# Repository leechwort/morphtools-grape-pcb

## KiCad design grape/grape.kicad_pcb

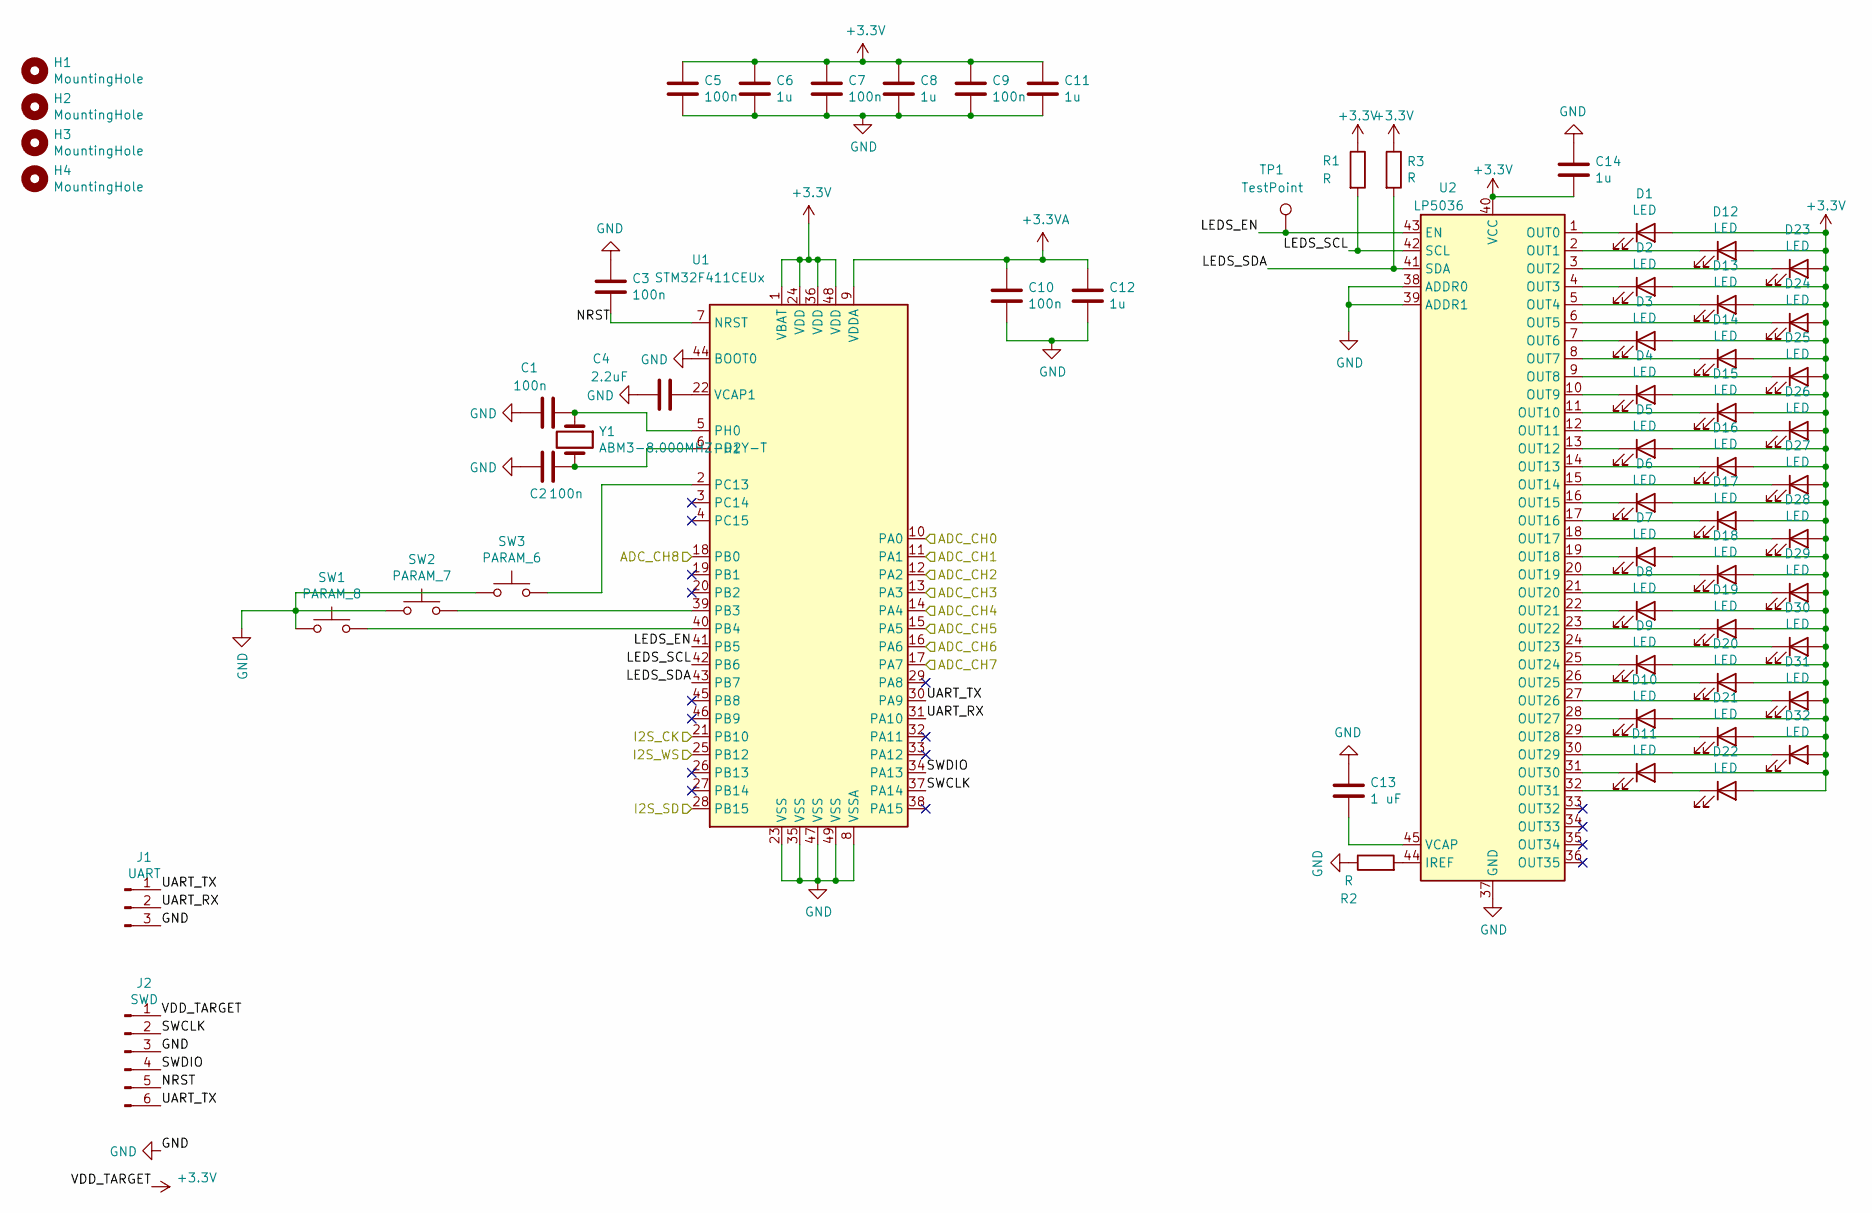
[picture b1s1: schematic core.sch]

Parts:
C1, C2, C3, C5, C7, C9, C10: 100n; C_0805_2012Metric_Pad1.18x1.45mm_HandSolder
C4: 2.2uF; C_0805_2012Metric_Pad1.18x1.45mm_HandSolder
C6, C8, C11, C12, C14: 1u; C_0805_2012Metric_Pad1.18x1.45mm_HandSolder
C13: 1 uF; C_0805_2012Metric_Pad1.18x1.45mm_HandSolder
D1, D2, D3, D4, D5, D6, D7, D8, D9, D10, D11, D12, D13, D14, D15, D16, D17, D18, D19, D20, D21, D22, D23, D24, D25, D26, D27, D28, D29, D30, D31, D32: LED; LED_D3.0mm
H1, H2, H3, H4: MountingHole; MountingHole_3.2mm_M3_Pad_Via
J1: UART; Molex_PicoBlade_53047-0310_1x03_P1.25mm_Vertical
J2: SWD; Molex_PicoBlade_53047-0610_1x06_P1.25mm_Vertical
R1, R2, R3: R; R_0805_2012Metric_Pad1.20x1.40mm_HandSolder
SW1: PARAM_8; SW_SPST_TL3305A
SW2: PARAM_7; SW_SPST_TL3305A
SW3: PARAM_6; SW_SPST_TL3305A
TP1: TestPoint; TestPoint_Pad_D1.5mm
U1: STM32F411CEUx; QFN-48-1EP_7x7mm_P0.5mm_EP5.6x5.6mm
U2: LP5036; VQFN-46-1EP_5x6mm_P0.4mm_EP2.8x3.8mm
Y1: ABM3-8.000MHZ-D2Y-T; Crystal_SMD_5032-2Pin_5.0x3.2mm_HandSoldering

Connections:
+3.3VA: C10.1, C12.1, U1.9 (VDDA); also elsewhere on the board
+3V3: C5.1, C6.1, C7.1, C8.1, C9.1, C11.1, C14.2, D1.2 (A), D2.2 (A), D3.2 (A), D4.2 (A), D5.2 (A), D6.2 (A), D7.2 (A), D8.2 (A), D9.2 (A), D10.2 (A), D11.2 (A), D12.2 (A), D13.2 (A), D14.2 (A), D15.2 (A), D16.2 (A), D17.2 (A), D18.2 (A), D19.2 (A), D20.2 (A), D21.2 (A), D22.2 (A), D23.2 (A), D24.2 (A), D25.2 (A), D26.2 (A), D27.2 (A), D28.2 (A), D29.2 (A), D30.2 (A), D31.2 (A), D32.2 (A), J2.1, R1.1, R3.1, U1.1 (VBAT), U1.24 (VDD), U1.36 (VDD), U1.48 (VDD), U2.40 (VCC); also elsewhere on the board
/core/ADC_CH0: U1.10 (PA0); also elsewhere on the board
/core/ADC_CH1: U1.11 (PA1); also elsewhere on the board
/core/ADC_CH2: U1.12 (PA2); also elsewhere on the board
/core/ADC_CH3: U1.13 (PA3); also elsewhere on the board
/core/ADC_CH4: U1.14 (PA4); also elsewhere on the board
/core/ADC_CH5: U1.15 (PA5); also elsewhere on the board
/core/ADC_CH6: U1.16 (PA6); also elsewhere on the board
/core/ADC_CH7: U1.17 (PA7); also elsewhere on the board
/core/ADC_CH8: U1.18 (PB0); also elsewhere on the board
/core/I2S_CK: U1.21 (PB10); also elsewhere on the board
/core/I2S_SD: U1.28 (PB15); also elsewhere on the board
/core/I2S_WS: U1.25 (PB12); also elsewhere on the board
/core/LEDS_EN: TP1.1, U1.41 (PB5), U2.43 (EN)
/core/LEDS_SCL: R1.2, U1.42 (PB6), U2.42 (SCL)
/core/LEDS_SDA: R3.2, U1.43 (PB7), U2.41 (SDA)
/core/NRST: C3.2, J2.5, U1.7 (NRST)
/core/SWCLK: J2.2, U1.37 (PA14)
/core/SWDIO: J2.4, U1.34 (PA13)
/core/UART_RX: J1.2, U1.31 (PA10)
/core/UART_TX: J1.1, J2.6, U1.30 (PA9)
GND: C1.1, C2.1, C3.1, C4.1, C5.2, C6.2, C7.2, C8.2, C9.2, C10.2, C11.2, C12.2, C13.1, C14.1, J1.3, J2.3, R2.1, SW1.1, SW2.1, SW3.1, U1.8 (VSSA), U1.23 (VSS), U1.35 (VSS), U1.44 (BOOT0), U1.47 (VSS), U1.49 (VSS), U2.37 (GND), U2.38 (ADDR0), U2.39 (ADDR1), U2.46 (GND), U2.47 (GND); also elsewhere on the board
unnamed: C1.2, U1.5 (PH0), Y1.1
unnamed: C2.2, U1.6 (PH1), Y1.2
unnamed: C4.2, U1.22 (VCAP1)
unnamed: C13.2, U2.45 (VCAP)
unnamed: D1.1 (K), U2.1 (OUT0)
unnamed: D2.1 (K), U2.4 (OUT3)
unnamed: D3.1 (K), U2.7 (OUT6)
unnamed: D4.1 (K), U2.10 (OUT9)
unnamed: D5.1 (K), U2.13 (OUT12)
unnamed: D6.1 (K), U2.16 (OUT15)
unnamed: D7.1 (K), U2.19 (OUT18)
unnamed: D8.1 (K), U2.22 (OUT21)
unnamed: D9.1 (K), U2.25 (OUT24)
unnamed: D10.1 (K), U2.28 (OUT27)
unnamed: D11.1 (K), U2.31 (OUT30)
unnamed: D12.1 (K), U2.2 (OUT1)
unnamed: D13.1 (K), U2.5 (OUT4)
unnamed: D14.1 (K), U2.8 (OUT7)
unnamed: D15.1 (K), U2.11 (OUT10)
unnamed: D16.1 (K), U2.14 (OUT13)
unnamed: D17.1 (K), U2.17 (OUT16)
unnamed: D18.1 (K), U2.20 (OUT19)
unnamed: D19.1 (K), U2.23 (OUT22)
unnamed: D20.1 (K), U2.26 (OUT25)
unnamed: D21.1 (K), U2.29 (OUT28)
unnamed: D22.1 (K), U2.32 (OUT31)
unnamed: D23.1 (K), U2.3 (OUT2)
unnamed: D24.1 (K), U2.6 (OUT5)
unnamed: D25.1 (K), U2.9 (OUT8)
unnamed: D26.1 (K), U2.12 (OUT11)
unnamed: D27.1 (K), U2.15 (OUT14)
unnamed: D28.1 (K), U2.18 (OUT17)
unnamed: D29.1 (K), U2.21 (OUT20)
unnamed: D30.1 (K), U2.24 (OUT23)
unnamed: D31.1 (K), U2.27 (OUT26)
unnamed: D32.1 (K), U2.30 (OUT29)
unnamed: R2.2, U2.44 (IREF)
unnamed: SW1.2, U1.40 (PB4)
unnamed: SW2.2, U1.39 (PB3)
unnamed: SW3.2, U1.2 (PC13)

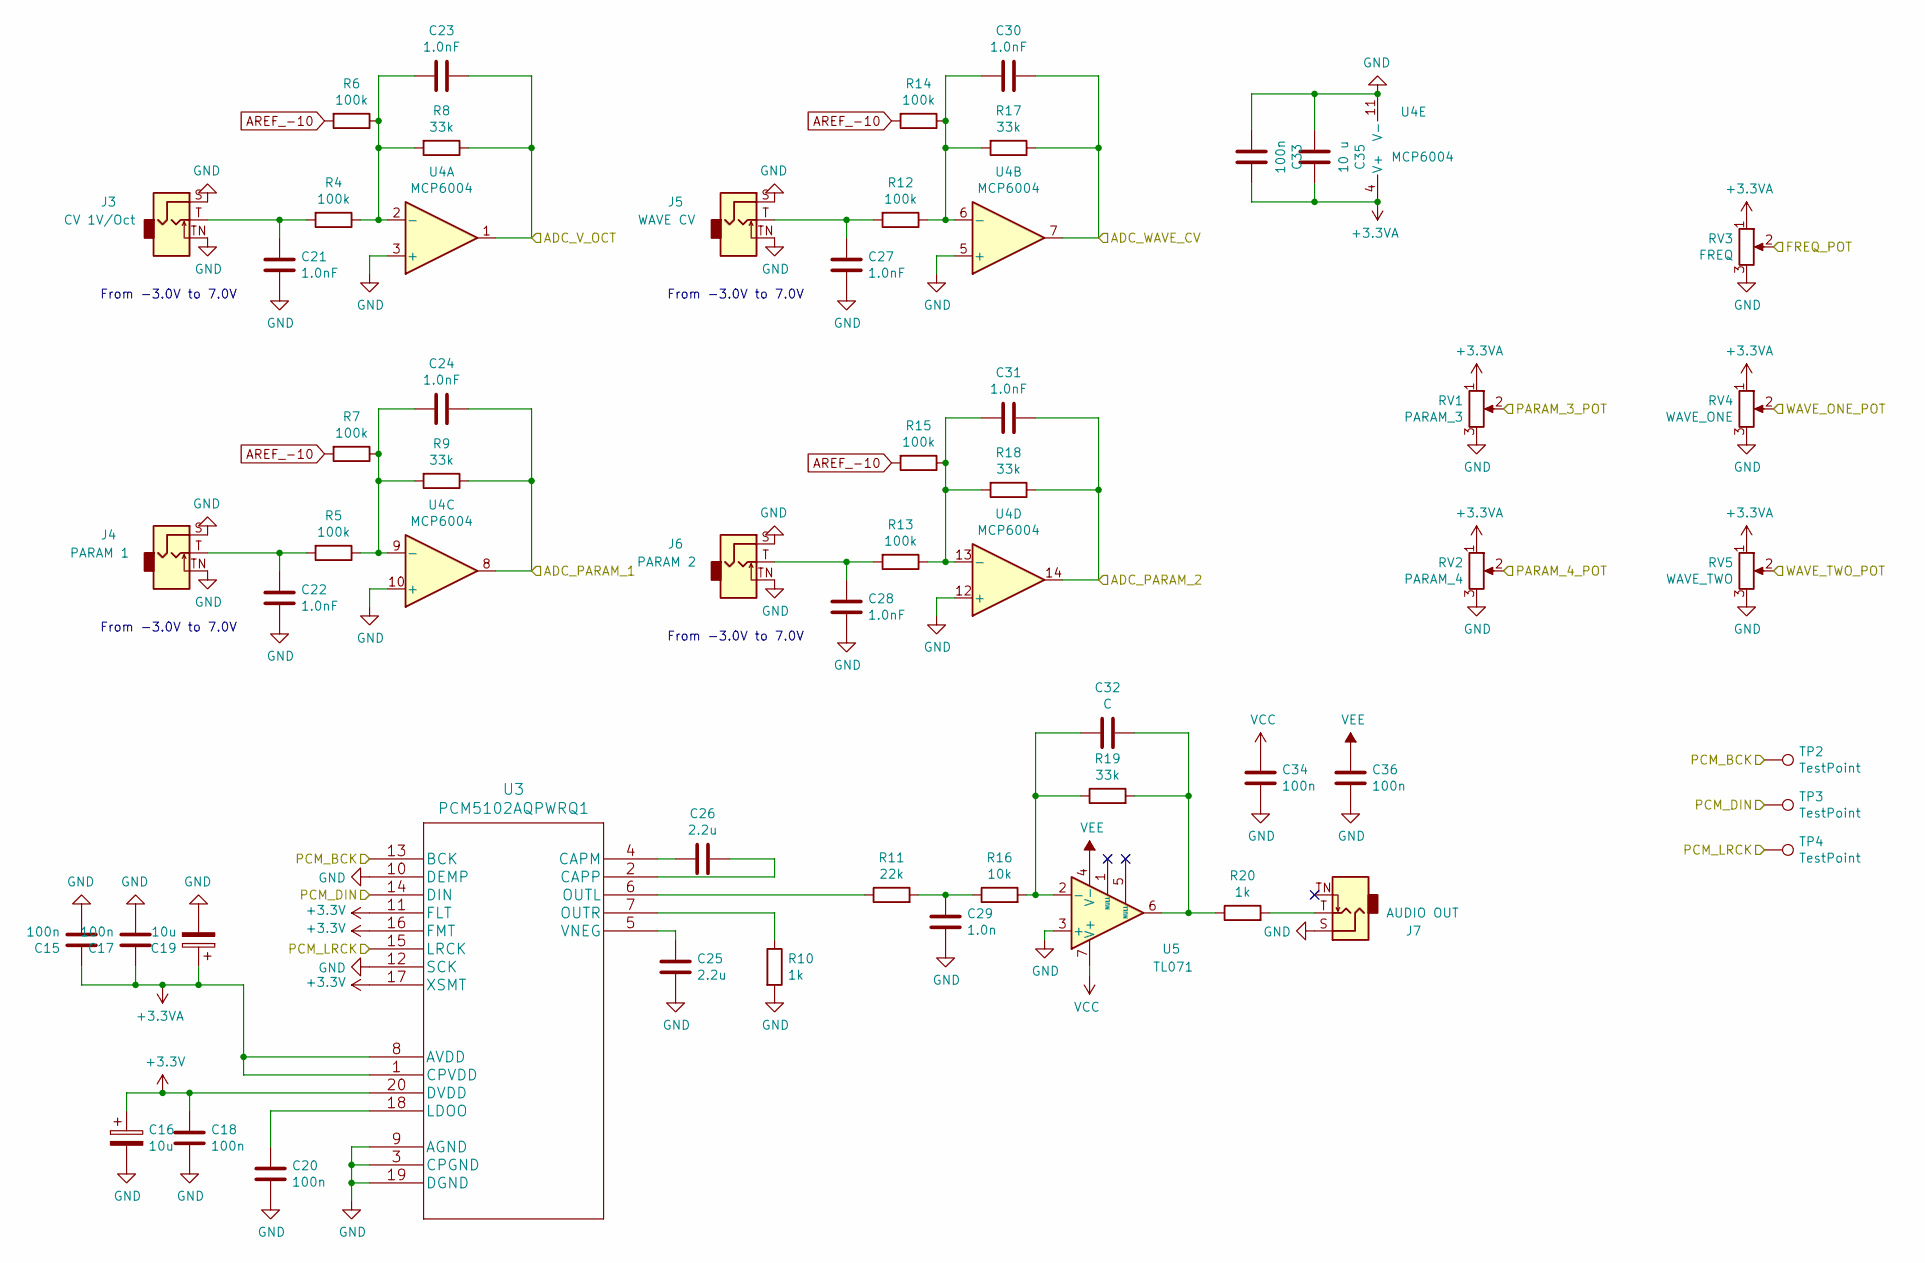
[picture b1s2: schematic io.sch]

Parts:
C15, C17, C18, C20, C33, C34, C36: 100n; C_0805_2012Metric_Pad1.18x1.45mm_HandSolder
C16, C19: 10u; C_0805_2012Metric_Pad1.18x1.45mm_HandSolder
C21, C22, C23, C24, C27, C28, C30, C31: 1.0nF; C_0805_2012Metric_Pad1.18x1.45mm_HandSolder
C25, C26: 2.2u; C_0805_2012Metric_Pad1.18x1.45mm_HandSolder
C29: 1.0n; C_0805_2012Metric_Pad1.18x1.45mm_HandSolder
C32: C; C_0805_2012Metric_Pad1.18x1.45mm_HandSolder
C35: 10 u; C_0805_2012Metric_Pad1.18x1.45mm_HandSolder
J3: CV 1V/Oct; Jack_3.5mm_QingPu_WQP-PJ398SM_Vertical_CircularHoles
J4: PARAM 1; Jack_3.5mm_QingPu_WQP-PJ398SM_Vertical_CircularHoles
J5: WAVE CV; Jack_3.5mm_QingPu_WQP-PJ398SM_Vertical_CircularHoles
J6: PARAM 2; Jack_3.5mm_QingPu_WQP-PJ398SM_Vertical_CircularHoles
J7: AUDIO OUT; Jack_3.5mm_QingPu_WQP-PJ398SM_Vertical_CircularHoles
R4, R5, R6, R7, R12, R13, R14, R15: 100k; R_0805_2012Metric_Pad1.20x1.40mm_HandSolder
R8, R9, R17, R18, R19: 33k; R_0805_2012Metric_Pad1.20x1.40mm_HandSolder
R10, R20: 1k; R_0805_2012Metric_Pad1.20x1.40mm_HandSolder
R11: 22k; R_0805_2012Metric_Pad1.20x1.40mm_HandSolder
R16: 10k; R_0805_2012Metric_Pad1.20x1.40mm_HandSolder
RV1: PARAM_3; Potentiometer_Alps_RK09L_Single_Vertical
RV2: PARAM_4; Potentiometer_Alps_RK09L_Single_Vertical
RV3: FREQ; Potentiometer_Alps_RK09L_Single_Vertical
RV4: WAVE_ONE; Potentiometer_Alps_RK09L_Single_Vertical
RV5: WAVE_TWO; Potentiometer_Alps_RK09L_Single_Vertical
TP2, TP3, TP4: TestPoint; TestPoint_Pad_D1.5mm
U3: PCM5102AQPWRQ1; TSSOP-20_4.4x6.5mm_P0.65mm
U4: MCP6004; TSSOP-14_4.4x5mm_P0.65mm
U5: TL071; SO-8_5.3x6.2mm_P1.27mm

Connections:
+3.3VA: C15.2, C17.2, C19.1, C33.1, C35.1, RV1.1, RV2.1, RV3.1, RV4.1, RV5.1, U3.1 (CPVDD), U3.8 (AVDD), U4.4 (V+); also elsewhere on the board
+3V3: C16.1, C18.2, U3.11 (FLT), U3.16 (FMT), U3.17 (XSMT), U3.20 (DVDD); also elsewhere on the board
/core/ADC_CH0: C23.1, R8.1, U4.1; also elsewhere on the board
/core/ADC_CH1: C24.1, R9.1, U4.8; also elsewhere on the board
/core/ADC_CH2: C31.1, R18.1, U4.14; also elsewhere on the board
/core/ADC_CH3: C30.1, R17.1, U4.7; also elsewhere on the board
/core/ADC_CH4: RV2.2; also elsewhere on the board
/core/ADC_CH5: RV1.2; also elsewhere on the board
/core/ADC_CH6: RV5.2; also elsewhere on the board
/core/ADC_CH7: RV4.2; also elsewhere on the board
/core/ADC_CH8: RV3.2; also elsewhere on the board
/core/I2S_CK: TP2.1, U3.13 (BCK); also elsewhere on the board
/core/I2S_SD: TP3.1, U3.14 (DIN); also elsewhere on the board
/core/I2S_WS: TP4.1, U3.15 (LRCK); also elsewhere on the board
AREF_-10: R6.2, R7.2, R14.2, R15.2; also elsewhere on the board
GND: C15.1, C16.2, C17.1, C18.1, C19.2, C20.1, C21.2, C22.2, C25.1, C27.2, C28.2, C29.1, C33.2, C34.1, C35.2, C36.1, J3.S, J3.TN, J4.S, J4.TN, J5.S, J5.TN, J6.S, J6.TN, J7.S, R10.2, RV1.3, RV2.3, RV3.3, RV4.3, RV5.3, U3.3 (CPGND), U3.9 (AGND), U3.10 (DEMP), U3.12 (SCK), U3.19 (DGND), U4.3 (+), U4.5 (+), U4.10 (+), U4.11 (V-), U4.12 (+), U5.3 (+); also elsewhere on the board
unnamed: C20.2, U3.18 (LDOO)
unnamed: C21.1, J3.T, R4.2
unnamed: C22.1, J4.T, R5.2
unnamed: C23.2, R4.1, R6.1, R8.2, U4.2 (-)
unnamed: C24.2, R5.1, R7.1, R9.2, U4.9 (-)
unnamed: C25.2, U3.5 (VNEG)
unnamed: C26.1, U3.2 (CAPP)
unnamed: C26.2, U3.4 (CAPM)
unnamed: C27.1, J5.T, R12.2
unnamed: C28.1, J6.T, R13.2
unnamed: C29.2, R11.2, R16.1
unnamed: C30.2, R12.1, R14.1, R17.2, U4.6 (-)
unnamed: C31.2, R13.1, R15.1, R18.2, U4.13 (-)
unnamed: C32.1, R19.2, R20.1, U5.6
unnamed: C32.2, R16.2, R19.1, U5.2 (-)
unnamed: J7.T, R20.2
unnamed: R10.1, U3.7 (OUTR)
unnamed: R11.1, U3.6 (OUTL)
VCC: C34.2, U5.7 (V+); also elsewhere on the board
VEE: C36.2, U5.4 (V-); also elsewhere on the board

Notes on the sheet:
From -3.0V to 7.0V

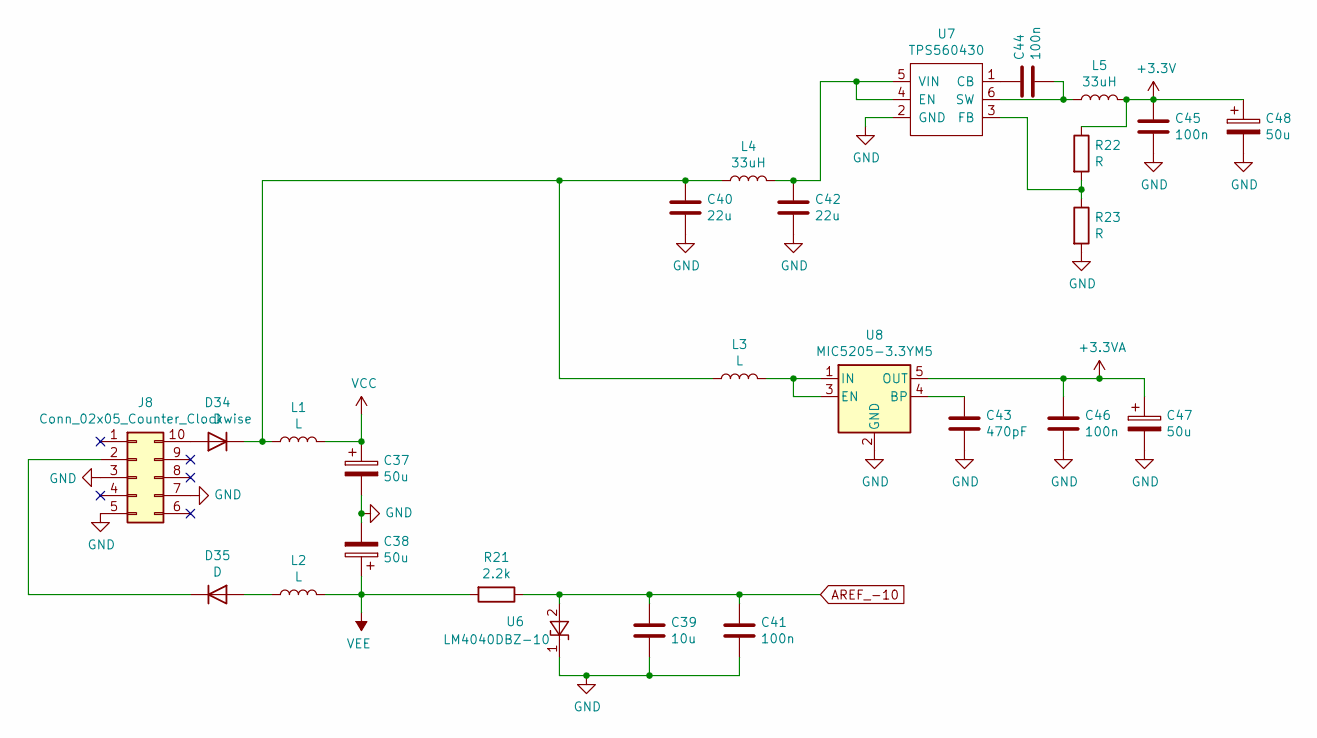
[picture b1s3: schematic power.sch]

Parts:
C37, C38, C48: 50u; CP_EIA-7343-31_Kemet-D_Pad2.25x2.55mm_HandSolder
C39: 10u; C_0805_2012Metric_Pad1.18x1.45mm_HandSolder
C40, C42: 22u; C_0805_2012Metric_Pad1.18x1.45mm_HandSolder
C41, C44, C45: 100n; C_0805_2012Metric_Pad1.18x1.45mm_HandSolder
C43: 470pF; C_0805_2012Metric_Pad1.18x1.45mm_HandSolder
C46: 100n; CP_EIA-7343-31_Kemet-D_Pad2.25x2.55mm_HandSolder
C47: 50u; CP_EIA-7343-30_AVX-N_Pad2.25x2.55mm_HandSolder
D34, D35: D; D_SMA-SMB_Universal_Handsoldering
J8: Conn_02x05_Counter_Clockwise; IDC-Header_2x05_P2.54mm_Vertical
L1, L2, L3: L; C_1206_3216Metric_Pad1.33x1.80mm_HandSolder
L4, L5: 33uH; L_Sumida_CDMC6D28_7.25x6.5mm
R21: 2.2k; R_0805_2012Metric_Pad1.20x1.40mm_HandSolder
R22, R23: R; R_0805_2012Metric_Pad1.20x1.40mm_HandSolder
U6: LM4040DBZ-10; SOT-23
U7: TPS560430; SOT-23-6_Handsoldering
U8: MIC5205-3.3YM5; SOT-23-5

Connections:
+3.3VA: C46.1, C47.1, U8.5 (OUT); also elsewhere on the board
+3V3: C45.1, C48.1, L5.2, R22.1; also elsewhere on the board
AREF_-10: C39.1, C41.1, R21.1, U6.2 (A); also elsewhere on the board
GND: C37.2, C38.2, C39.2, C40.2, C41.2, C42.2, C43.2, C45.2, C46.2, C47.2, C48.2, J8.3, J8.5, J8.7, R23.2, U6.1 (K), U7.2 (GND), U8.2 (GND); also elsewhere on the board
unnamed: C40.1, D34.1 (K), L1.1, L3.1, L4.1
unnamed: C42.1, L4.2, U7.4 (EN), U7.5 (VIN)
unnamed: C43.1, U8.4 (BP)
unnamed: C44.1, U7.1 (CB)
unnamed: C44.2, L5.1, U7.6 (SW)
unnamed: D34.2 (A), J8.10
unnamed: D35.1 (K), J8.2
unnamed: D35.2 (A), L2.1
unnamed: L3.2, U8.1 (IN), U8.3 (EN)
unnamed: R22.2, R23.1, U7.3 (FB)
VCC: C37.1, L1.2; also elsewhere on the board
VEE: C38.1, L2.2, R21.2; also elsewhere on the board

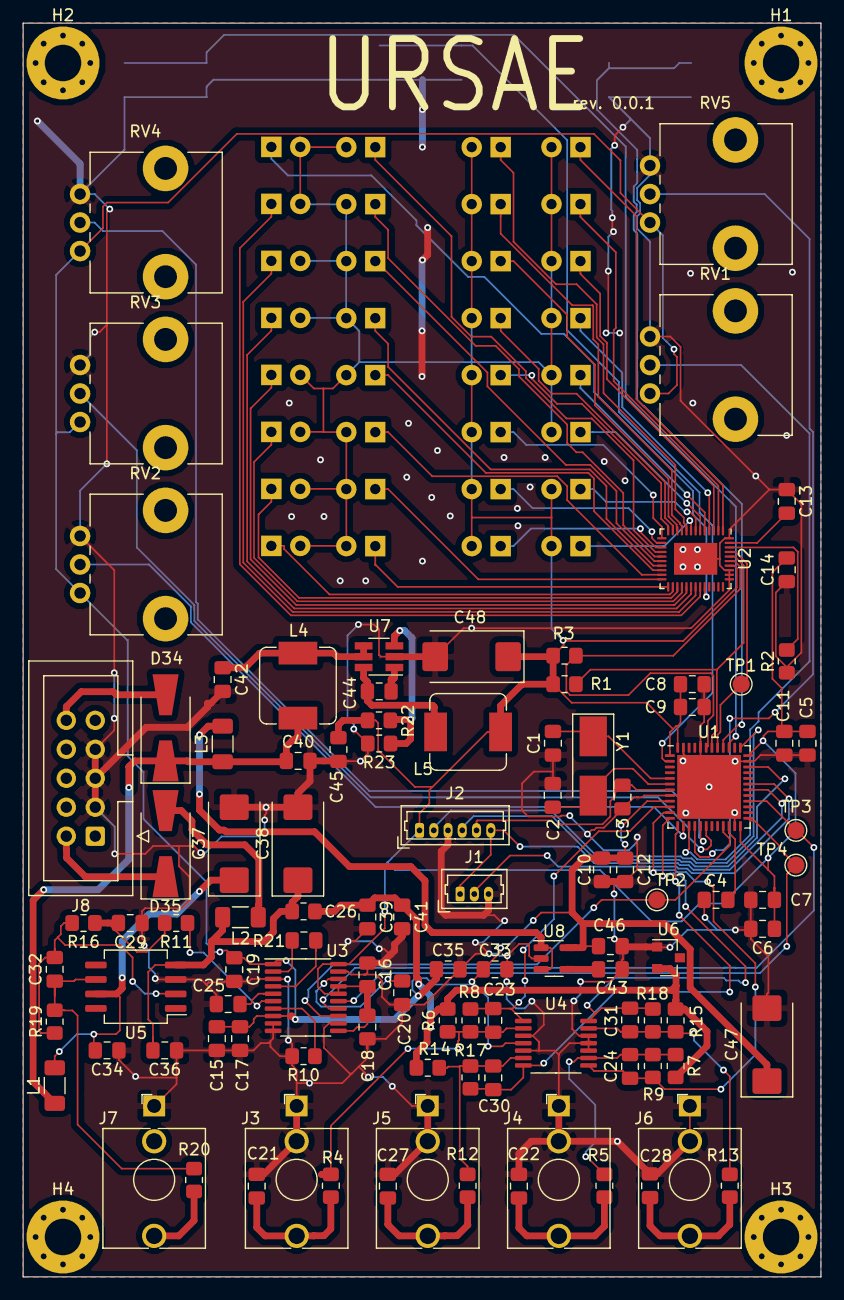
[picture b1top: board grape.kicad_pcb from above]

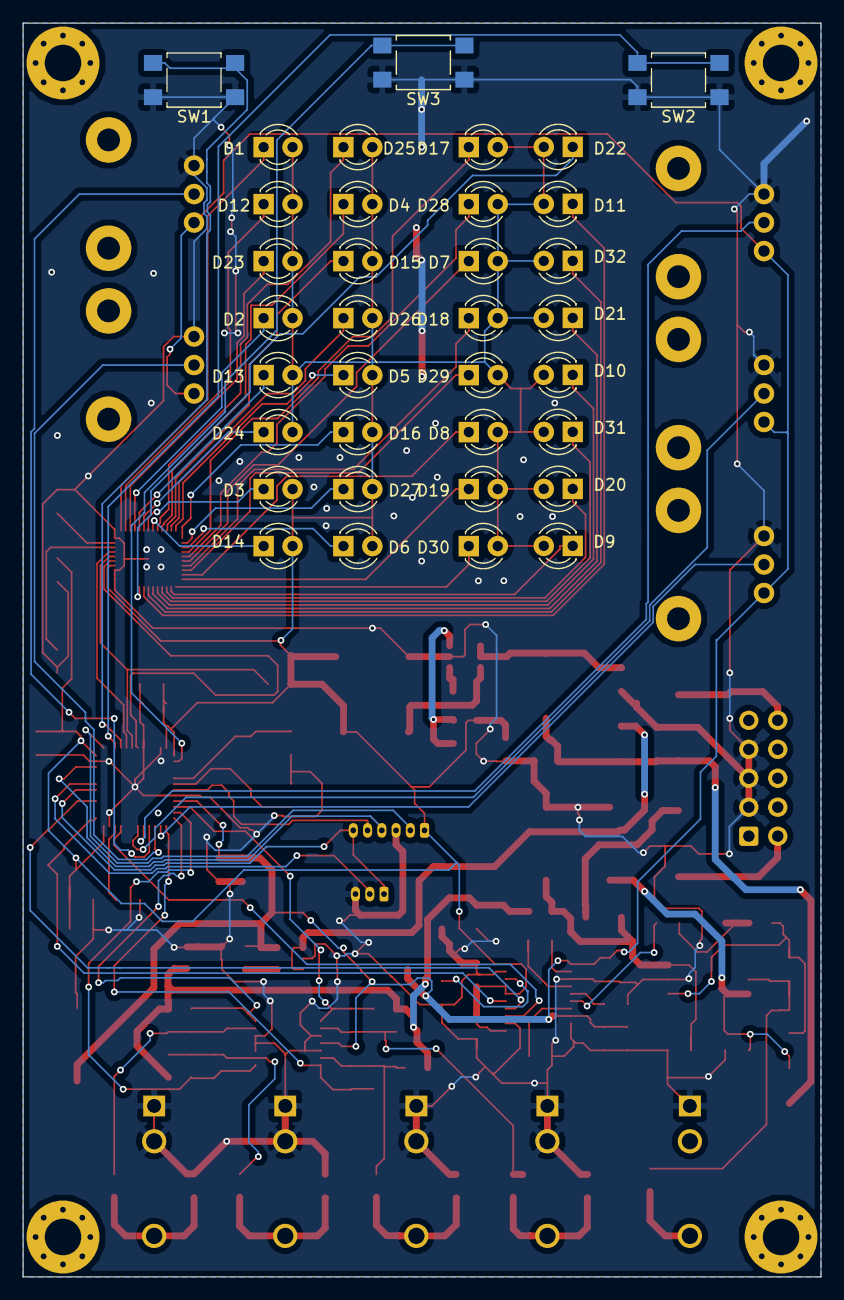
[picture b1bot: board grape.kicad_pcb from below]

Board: 2 copper layers, 70.0 x 110.0 mm, 143 parts (35 on the bottom side), 94 nets.

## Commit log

2020-12-06 Added schematic
2020-12-06 Annotation added
2020-12-06 Footprint assignment and some additions
2020-12-06 Switch to TPS560430 power
2020-12-07 Components placed
2020-12-07 Routing in progress
2020-12-08 Finished routing
2021-02-25 Alpha v0.0.1
2021-04-03 Something
